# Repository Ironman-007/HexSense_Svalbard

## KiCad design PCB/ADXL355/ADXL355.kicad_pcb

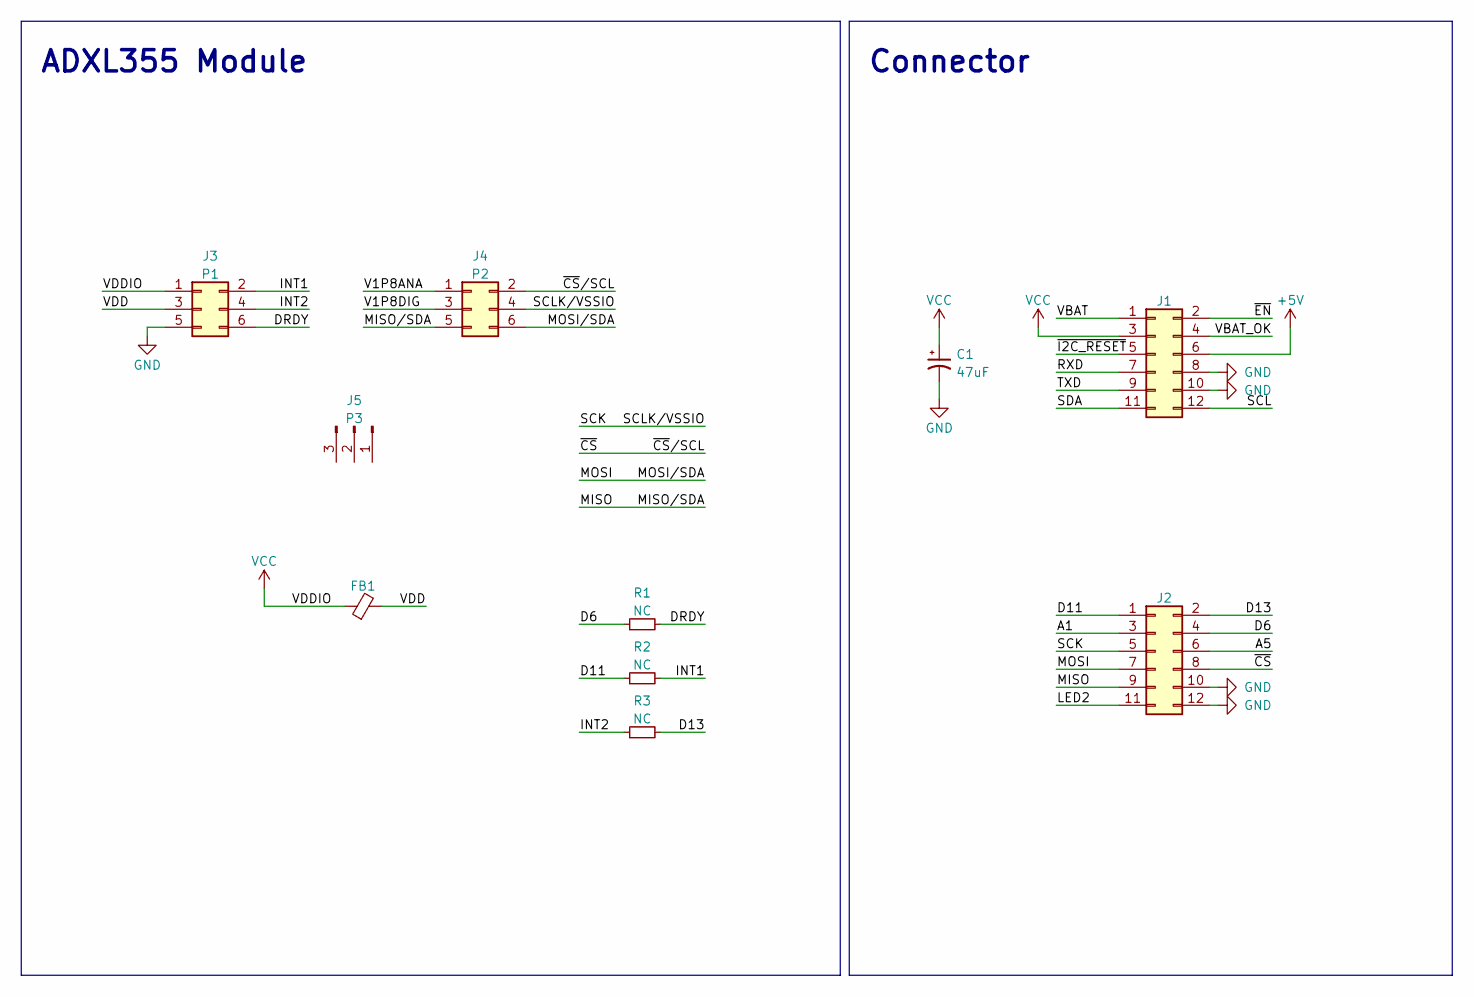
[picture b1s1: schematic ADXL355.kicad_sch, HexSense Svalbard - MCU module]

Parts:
C1: 47uF; LED_0805_2012Metric_Pad1.15x1.40mm_HandSolder
FB1: FerriteBead_Small; R_0603_1608Metric_Pad0.98x0.95mm_HandSolder
J1, J2: Conn_02x06_Odd_Even; PinHeader_2x06_P2.54mm_Vertical
J3: P1; PinHeader_2x03_P2.54mm_Vertical
J4: P2; PinHeader_2x03_P2.54mm_Vertical
J5: P3; PinHeader_1x03_P2.54mm_Vertical
R1, R2, R3: NC; R_0805_2012Metric

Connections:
+5V: J1.6
/A1: J2.3
/A5: J2.6
/D6: J2.4, R1.1
/D11: J2.1, R2.1
/D13: J2.2, R3.2
/DRDY: J3.6, R1.2
/INT1: J3.2, R2.2
/INT2: J3.4, R3.1
/LED2: J2.11
/MISO: J2.9, J4.5
/MOSI: J2.7, J4.6
/RXD: J1.7
/SCK: J2.5, J4.4
/SCL: J1.12
/SDA: J1.11
/TXD: J1.9
/V1P8ANA: J4.1
/V1P8DIG: J4.3
/VBAT: J1.1
/VBAT_OK: J1.4
/VDD: FB1.2, J3.3
/~CS: J2.8, J4.2
/~EN: J1.2
/~I2C_RESET: J1.5
GND: C1.2, J1.8, J1.10, J2.10, J2.12, J3.5
VCC: C1.1, FB1.1, J1.3, J3.1

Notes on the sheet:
ADXL355 Module
Connector

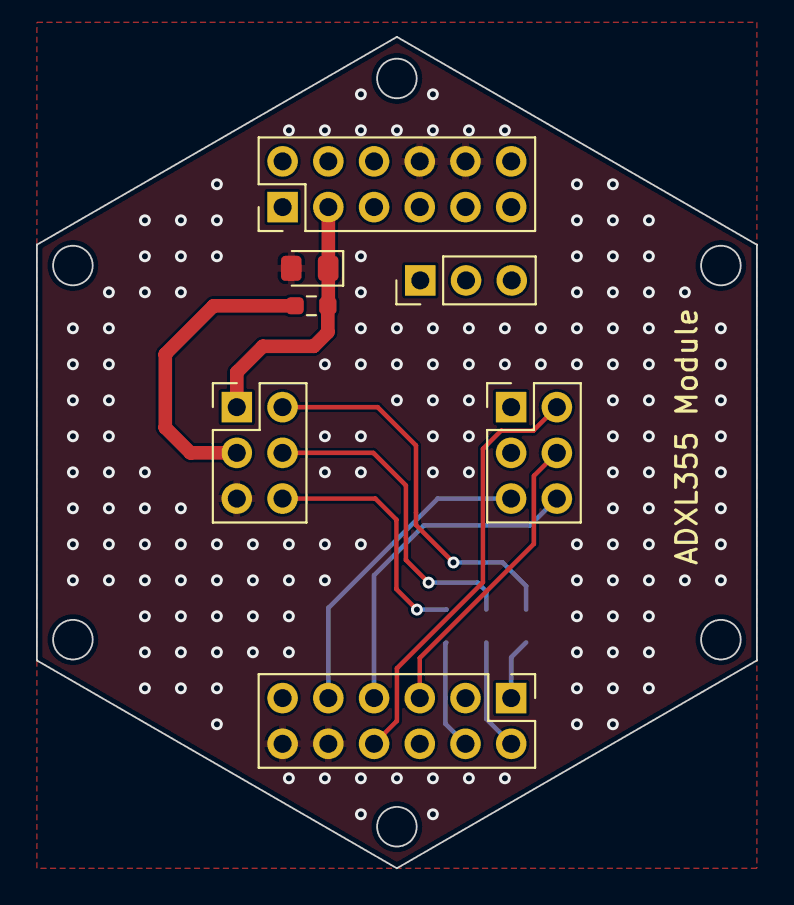
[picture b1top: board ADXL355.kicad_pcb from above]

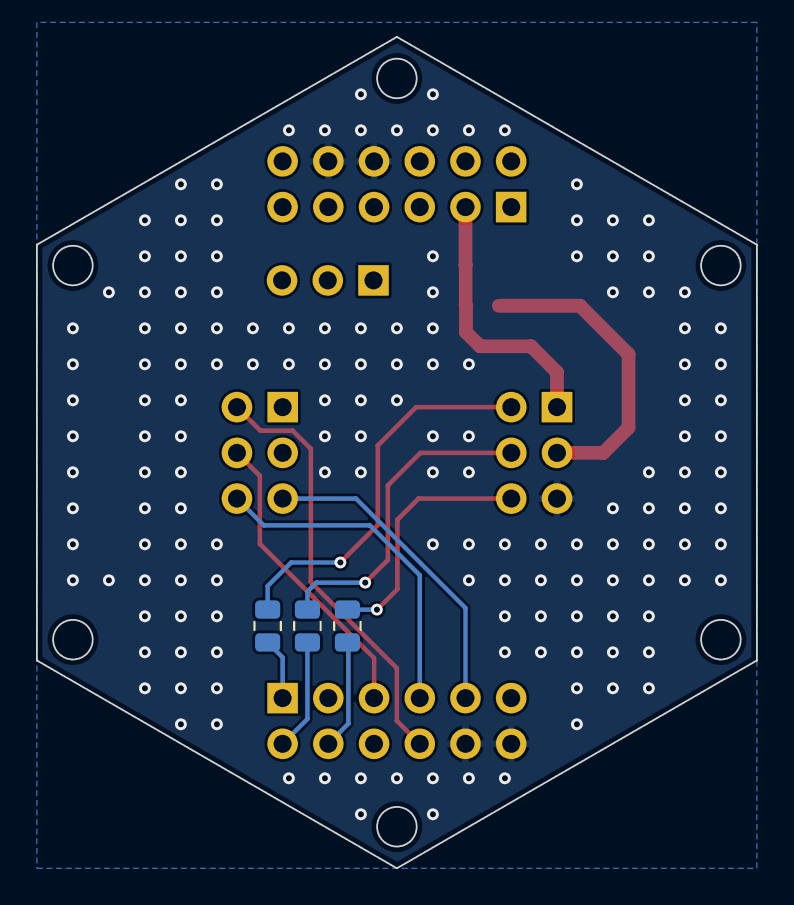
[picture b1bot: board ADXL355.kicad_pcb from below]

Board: 2 copper layers, 40.0 x 46.2 mm, 10 parts (3 on the bottom side), 13 nets.

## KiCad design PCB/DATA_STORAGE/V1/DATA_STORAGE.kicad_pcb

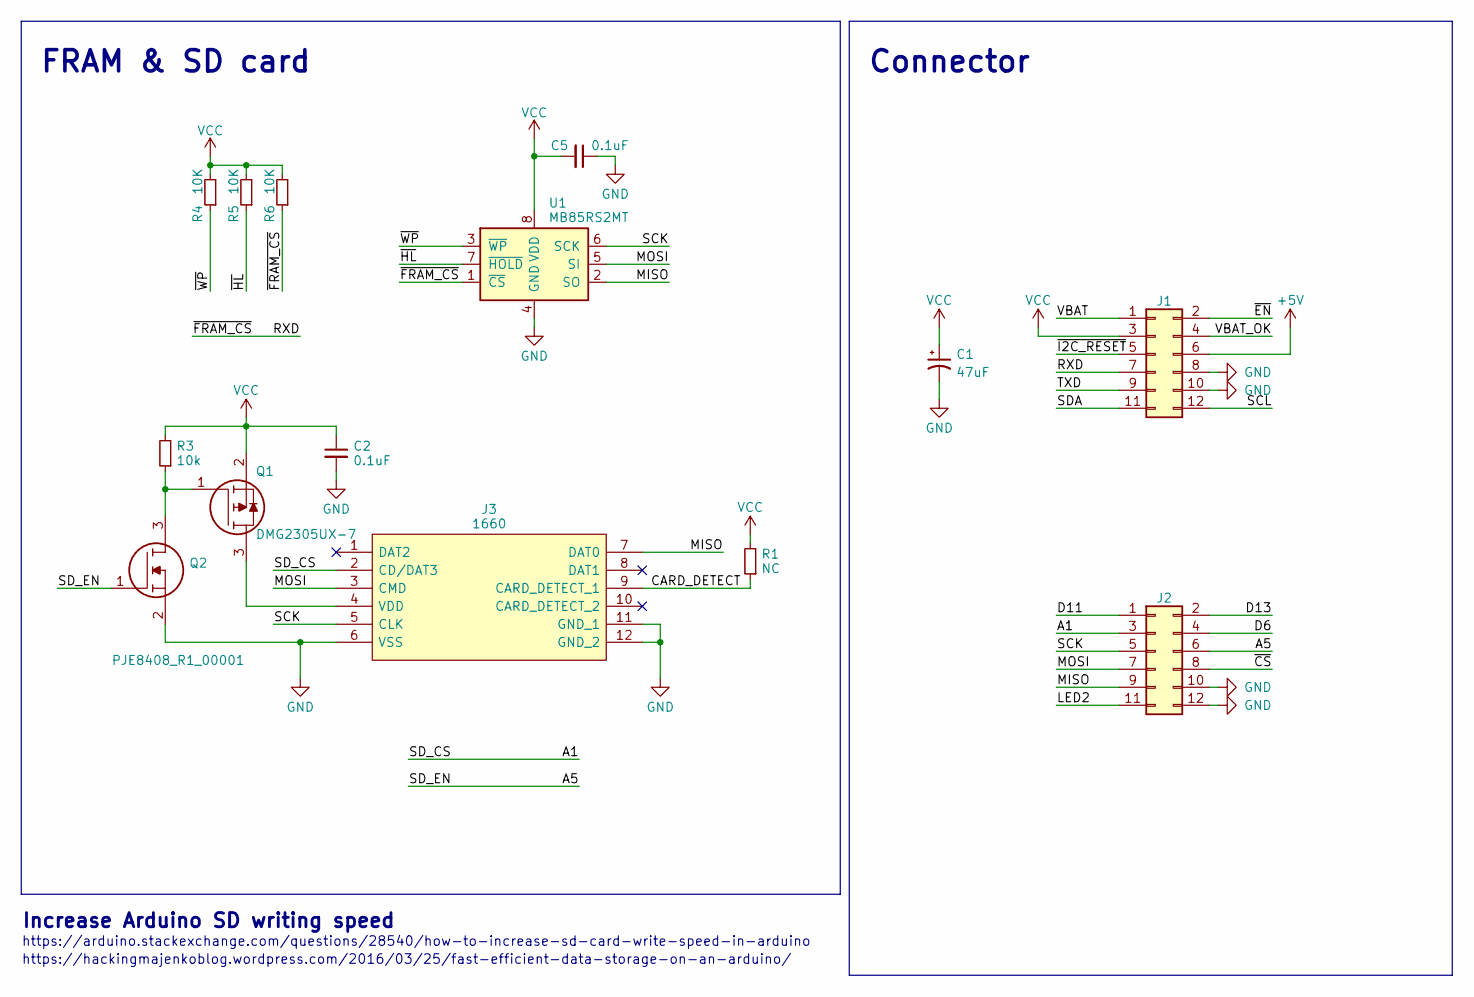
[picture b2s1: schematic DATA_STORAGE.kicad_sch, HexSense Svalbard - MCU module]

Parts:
C1: 47uF; LED_0805_2012Metric_Pad1.15x1.40mm_HandSolder
C2, C5: 0.1uF; C_0603_1608Metric_Pad1.08x0.95mm_HandSolder
J1, J2: Conn_02x06_Odd_Even; PinHeader_2x06_P2.54mm_Vertical
J3: 1660; Manufacturer_Part_Number 1660; Mouser Part Number 485-1660
Q1: DMG2305UX-7; SOT96P240X110-3N; Manufacturer_Part_Number DMG2305UX-7; Mouser Part Number 621-DMG2305UX-7
Q2: PJE8408_R1_00001; SOTFL50P160X60-3N; Manufacturer_Part_Number PJE8408_R1_00001; Mouser Part Number 241-PJE8408_R1_00001
R1: NC; R_0603_1608Metric_Pad0.98x0.95mm_HandSolder
R3: 10k; R_0603_1608Metric_Pad0.98x0.95mm_HandSolder
R4, R5, R6: 10K; R_0603_1608Metric_Pad0.98x0.95mm_HandSolder
U1: MB85RS2MT; SSOP-8_3.9x5.05mm_P1.27mm

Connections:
+5V: J1.6
/A1: J2.3, J3.2 (CD/DAT3)
/A5: J2.6, Q2.1
/CARD_DETECT: J3.9 (CARD_DETECT_1), R1.1
/D6: J2.4
/D11: J2.1
/D13: J2.2
/LED2: J2.11
/MISO: J2.9, J3.7 (DAT0), U1.2 (SO)
/MOSI: J2.7, J3.3 (CMD), U1.5 (SI)
/RXD: J1.7, R6.1, U1.1 (~CS)
/SCK: J2.5, J3.5 (CLK), U1.6 (SCK)
/SCL: J1.12
/SDA: J1.11
/TXD: J1.9
/VBAT: J1.1
/VBAT_OK: J1.4
/~CS: J2.8
/~EN: J1.2
/~HL: R5.1, U1.7 (~HOLD)
/~I2C_RESET: J1.5
/~WP: R4.1, U1.3 (~WP)
GND: C1.2, C2.2, C5.1, J1.8, J1.10, J2.10, J2.12, J3.6 (VSS), J3.11 (GND_1), J3.12 (GND_2), Q2.2, U1.4 (GND)
unnamed: J3.4 (VDD), Q1.3
unnamed: Q1.1, Q2.3, R3.1
VCC: C1.1, C2.1, C5.2, J1.3, Q1.2, R1.2, R3.2, R4.2, R5.2, R6.2, U1.8 (VDD)

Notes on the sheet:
https://arduino.stackexchange.com/questions/28540/how-to-increase-sd-card-write-speed-in-arduino
FRAM & SD card
Increase Arduino SD writing speed
https://hackingmajenkoblog.wordpress.com/2016/03/25/fast-efficient-data-storage-on-an-arduino/
Connector

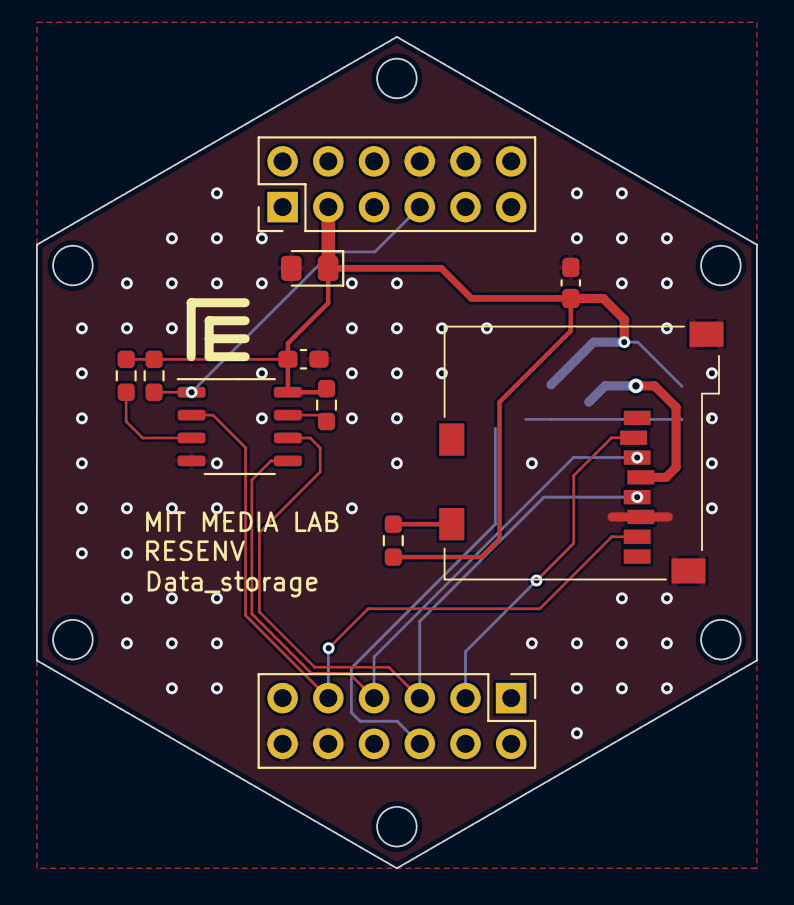
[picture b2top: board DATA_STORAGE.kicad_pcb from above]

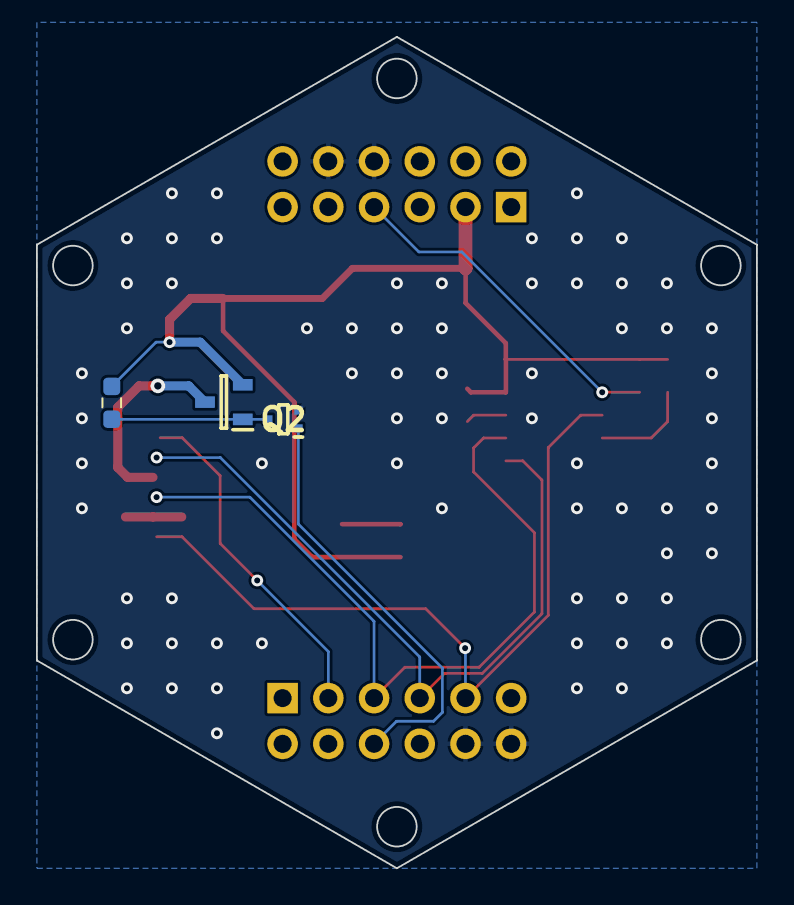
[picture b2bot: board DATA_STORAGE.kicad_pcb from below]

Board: 2 copper layers, 40.0 x 46.2 mm, 14 parts (3 on the bottom side), 13 nets.

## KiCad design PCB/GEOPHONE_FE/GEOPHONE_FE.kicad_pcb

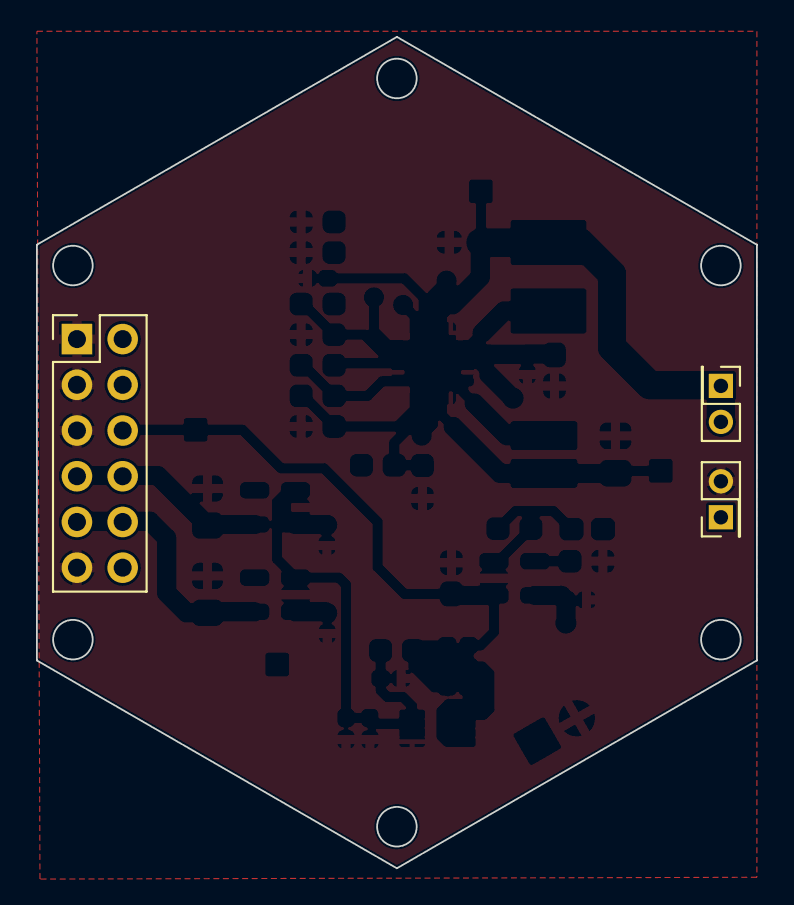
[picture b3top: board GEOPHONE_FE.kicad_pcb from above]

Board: 2 copper layers, 40.0 x 46.2 mm, 3 parts (0 on the bottom side), 5 nets, no tracks yet.

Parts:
J2: Conn_02x06_Odd_Even; PinHeader_2x06_P2.54mm_Vertical
J3: Battery; PinHeader_2x01_P2.00mm_Vertical
J4: Solar cell; PinHeader_2x01_P2.00mm_Vertical

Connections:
+1V8: J2.9, J2.10
+3V3: J2.7, J2.8
/SC: J4.1, J4.2
/VBAT: J2.6, J3.1
GND: J2.1, J2.3, J2.5, J2.11, J3.2

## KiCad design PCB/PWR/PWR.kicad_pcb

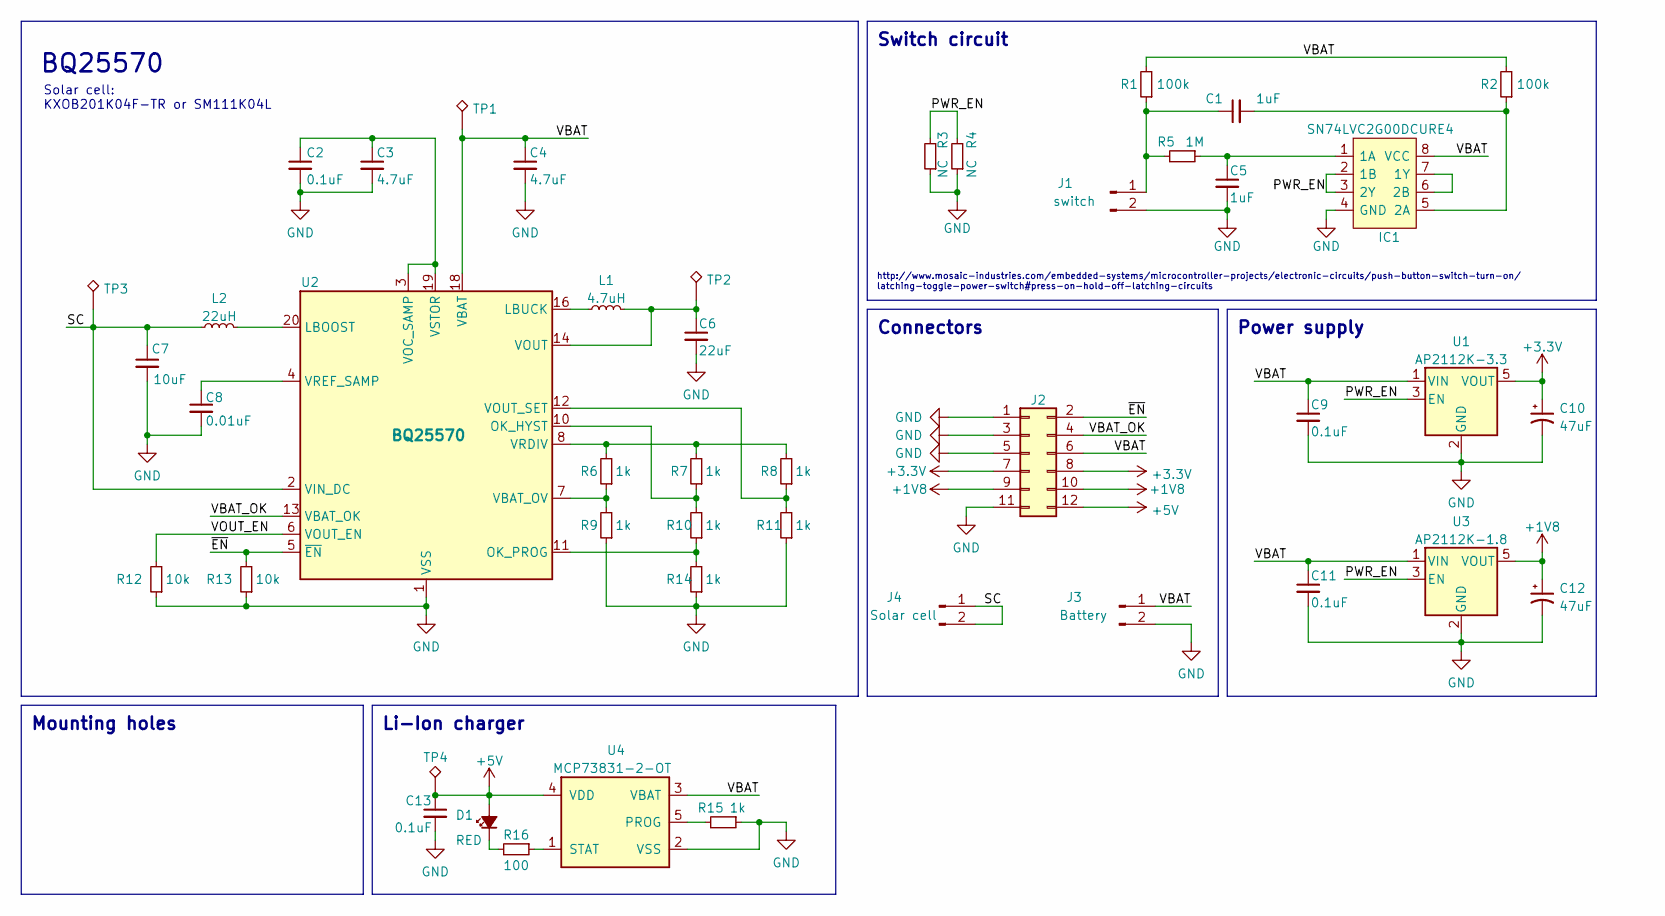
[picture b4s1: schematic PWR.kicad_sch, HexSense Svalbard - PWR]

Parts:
C1, C5: 1uF; C_0402_1005Metric_Pad0.74x0.62mm_HandSolder
C2, C9, C11, C13: 0.1uF; C_0402_1005Metric_Pad0.74x0.62mm_HandSolder
C3, C4: 4.7uF; C_0603_1608Metric_Pad1.08x0.95mm_HandSolder
C6: 22uF; C_0805_2012Metric_Pad1.18x1.45mm_HandSolder
C7: 10uF; C_0603_1608Metric_Pad1.08x0.95mm_HandSolder
C8: 0.01uF; C_0402_1005Metric_Pad0.74x0.62mm_HandSolder
C10, C12: 47uF; LED_0805_2012Metric_Pad1.15x1.40mm_HandSolder
D1: RED; LED_0603_1608Metric_Pad1.05x0.95mm_HandSolder
IC1: SN74LVC2G00DCURE4; SOP50P310X90-8N; Manufacturer_Part_Number SN74LVC2G00DCURE4
J1: switch; PinHeader_1x02_P2.54mm_Vertical
J2: Conn_02x06_Odd_Even; PinHeader_2x06_P2.54mm_Vertical
J3: Battery; PinHeader_2x01_P2.00mm_Vertical
J4: Solar cell; PinHeader_2x01_P2.00mm_Vertical
L1: 4.7uH; L_Wuerth_MAPI-3015
L2: 22uH; L_Taiyo-Yuden_NR-40xx_HandSoldering
R1, R2: 100k; R_0402_1005Metric_Pad0.72x0.64mm_HandSolder
R3, R4: NC; R_0402_1005Metric_Pad0.72x0.64mm_HandSolder
R5: 1M; R_0603_1608Metric_Pad0.98x0.95mm_HandSolder
R6, R7, R8, R9, R10, R11, R14, R15: 1k; R_0603_1608Metric_Pad0.98x0.95mm_HandSolder
R12, R13: 10k; R_0603_1608Metric_Pad0.98x0.95mm_HandSolder
R16: 100; R_0603_1608Metric_Pad0.98x0.95mm_HandSolder
TP1, TP2, TP3, TP4: TestPoint_Alt; TestPoint_Pad_1.0x1.0mm
U1: AP2112K-3.3; SOT-23-5
U2: BQ25570; QFN-20-1EP_3.5x3.5mm_P0.5mm_EP2x2mm
U3: AP2112K-1.8; SOT-23-5
U4: MCP73831-2-OT; SOT-23-5

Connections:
+1V8: C12.1, J2.9, J2.10, U3.5 (VOUT)
+3V3: C10.1, J2.7, J2.8, U1.5 (VOUT)
+5V: C13.1, D1.2 (A), J2.12, TP4.1, U4.4 (VDD)
/PWR_EN: IC1.2 (1B), IC1.3 (2Y), R3.2, R4.2, U1.3 (EN), U3.3 (EN)
/SC: C7.1, J4.1, J4.2, L2.1, TP3.1, U2.2 (VIN_DC)
/VBAT: C4.1, C9.1, C11.1, IC1.8 (VCC), J2.6, J3.1, R1.2, R2.2, TP1.1, U1.1 (VIN), U2.18 (VBAT), U3.1 (VIN), U4.3 (VBAT)
/VBAT_OK: J2.4, U2.13 (VBAT_OK)
/VOUT_EN: R12.2, U2.6 (VOUT_EN)
/~EN: J2.2, R13.2, U2.5 (~EN)
GND: C2.2, C3.2, C4.2, C5.2, C6.2, C7.2, C8.2, C9.2, C10.2, C11.2, C12.2, C13.2, IC1.4 (GND), J1.2, J2.1, J2.3, J2.5, J2.11, J3.2, R3.1, R4.1, R9.1, R11.1, R12.1, R13.1, R14.1, R15.1, U1.2 (GND), U2.1 (VSS), U2.9 (VSS), U2.15 (VSS), U2.17 (VSS), U2.21 (VSS), U3.2 (GND), U4.2 (VSS)
unnamed: C1.1, J1.1, R1.1, R5.2
unnamed: C1.2, IC1.5 (2A), R2.1
unnamed: C2.1, C3.1, U2.3 (VOC_SAMP), U2.19 (VSTOR)
unnamed: C5.1, IC1.1 (1A), R5.1
unnamed: C6.1, L1.2, TP2.1, U2.14 (VOUT)
unnamed: C8.1, U2.4 (VREF_SAMP)
unnamed: D1.1 (K), R16.2
unnamed: IC1.6 (2B), IC1.7 (1Y)
unnamed: L1.1, U2.16 (LBUCK)
unnamed: L2.2, U2.20 (LBOOST)
unnamed: R6.1, R9.2, U2.7 (VBAT_OV)
unnamed: R6.2, R7.2, R8.2, U2.8 (VRDIV)
unnamed: R10.1, R14.2, U2.11 (OK_PROG)
unnamed: R7.1, R10.2, U2.10 (OK_HYST)
unnamed: R8.1, R11.2, U2.12 (VOUT_SET)
unnamed: R15.2, U4.5 (PROG)
unnamed: R16.1, U4.1 (STAT)

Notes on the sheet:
Li-Ion charger
BQ25570
Switch circuit
Mounting holes
Solar cell: KXOB201K04F-TR or SM111K04L
Power supply
http://www.mosaic-industries.com/embedded-systems/microcontroller-projects/electronic-circuits/push-button-switch-turn-on/ latching-toggle-power-switch#press-on-hold-off-latching-circuits
Connectors

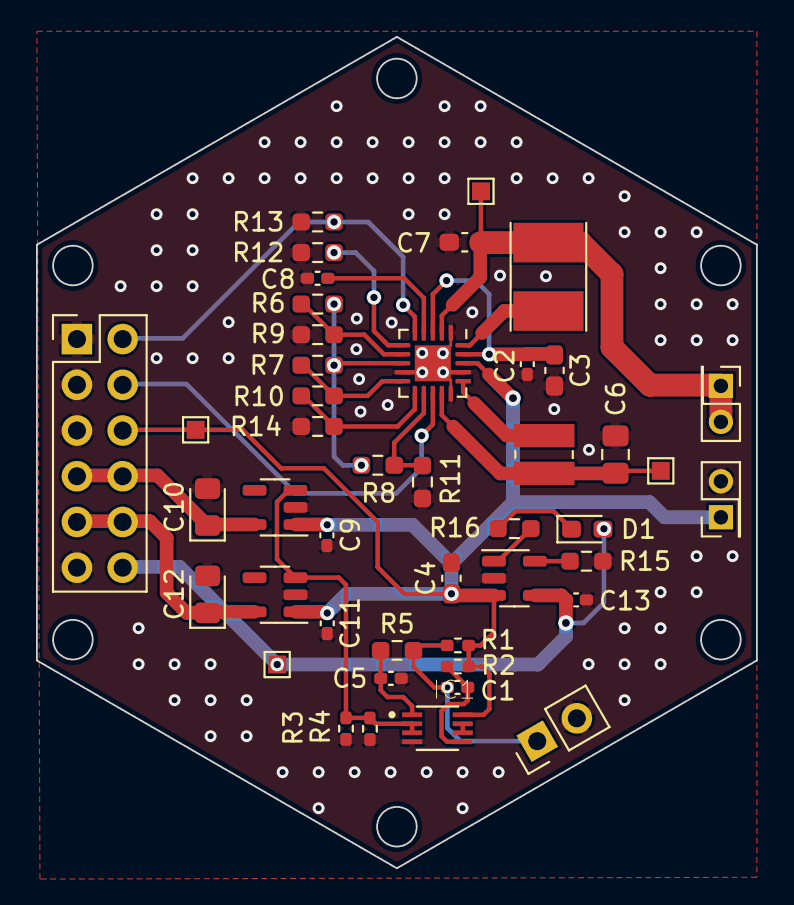
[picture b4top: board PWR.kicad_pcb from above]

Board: 2 copper layers, 40.0 x 46.2 mm, 45 parts (0 on the bottom side), 27 nets.

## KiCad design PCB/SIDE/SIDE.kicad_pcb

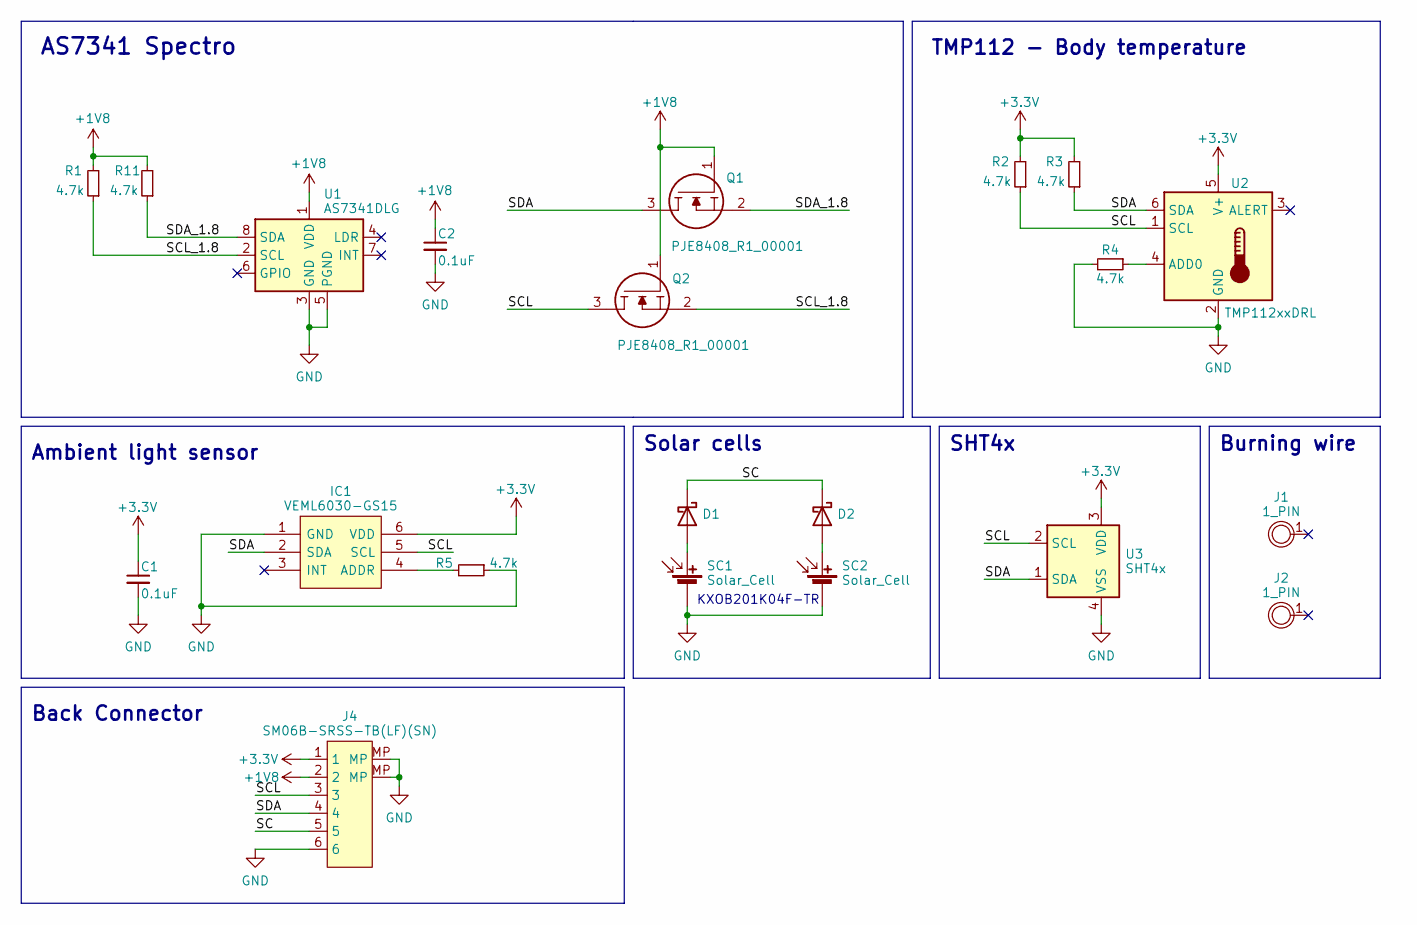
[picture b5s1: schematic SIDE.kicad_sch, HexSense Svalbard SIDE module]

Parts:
C1, C2: 0.1uF; C_0603_1608Metric_Pad1.08x0.95mm_HandSolder
D1, D2: D_Schottky; D_0805_2012Metric_Pad1.15x1.40mm_HandSolder
IC1: VEML6030-GS15; VEML6030GS15; Manufacturer_Part_Number VEML6030-GS15; Mouser Part Number 78-VEML6030-GS15
J1, J2: 1_PIN; 1_pin_SMD_1.5mmx1.0mm
J4: SM06B-SRSS-TB(LF)(SN); JST_SH_SM06B-SRSS-TB_1x06-1MP_P1.00mm_Horizontal
Q1, Q2: PJE8408_R1_00001; SOTFL50P160X60-3N; Manufacturer_Part_Number PJE8408_R1_00001; Mouser Part Number 241-PJE8408_R1_00001
R1, R2, R3, R4, R5, R11: 4.7k; R_0603_1608Metric_Pad0.98x0.95mm_HandSolder
SC1, SC2: Solar_Cell; KXOB201K04F-TR
U1: AS7341DLG; AMS_OLGA-8_2x3.1mm_P0.8mm
U2: TMP112xxDRL; SOT-563
U3: SHT4x; Sensirion_DFN-4_1.5x1.5mm_P0.8mm_SHT4x_NoCentralPad

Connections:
+1V8: C2.1, J4.2, Q1.1, Q2.1, R1.2, R11.2, U1.1 (VDD)
+3V3: C1.1, IC1.6 (VDD), J4.1, R2.2, R3.2, U2.5 (V+), U3.3 (VDD)
/SC: D1.1 (K), D2.1 (K), J4.5
/SCL: IC1.5 (SCL), J4.3, Q2.3, R2.1, U2.1 (SCL), U3.2 (SCL)
/SCL_1.8: Q2.2, R1.1, U1.2 (SCL)
/SDA: IC1.2 (SDA), J4.4, Q1.3, R3.1, U2.6 (SDA), U3.1 (SDA)
/SDA_1.8: Q1.2, R11.1, U1.8 (SDA)
GND: C1.2, C2.2, IC1.1 (GND), J4.6, J4.MP, R4.2, R5.1, SC1.2 (-), SC2.2 (-), U1.3 (GND), U1.5 (PGND), U2.2 (GND), U3.4 (VSS)
unnamed: D1.2 (A), SC1.1 (+)
unnamed: D2.2 (A), SC2.1 (+)
unnamed: IC1.4 (ADDR), R5.2
unnamed: R4.1, U2.4 (ADD0)

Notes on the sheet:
Burning wire
Back Connector
TMP112 - Body temperature
KXOB201K04F-TR
Solar cells
SHT4x
AS7341 Spectro
Ambient light sensor

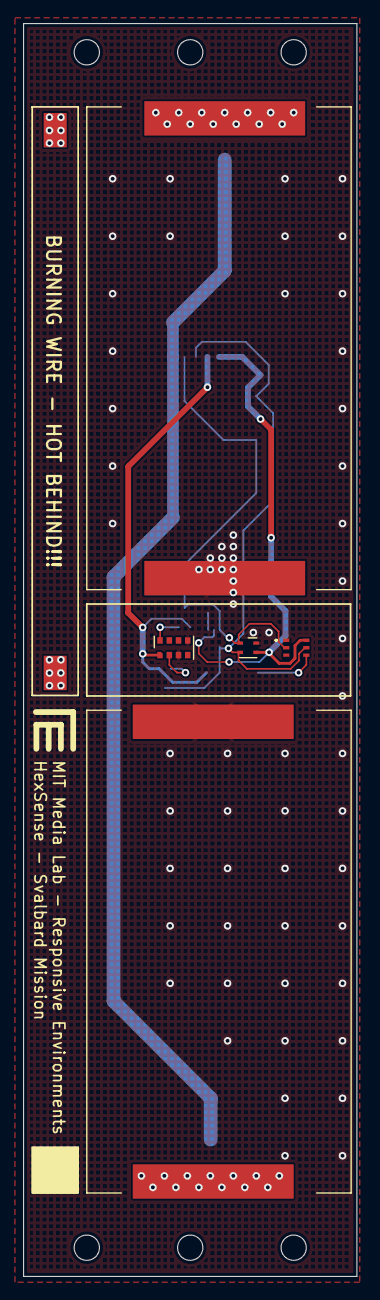
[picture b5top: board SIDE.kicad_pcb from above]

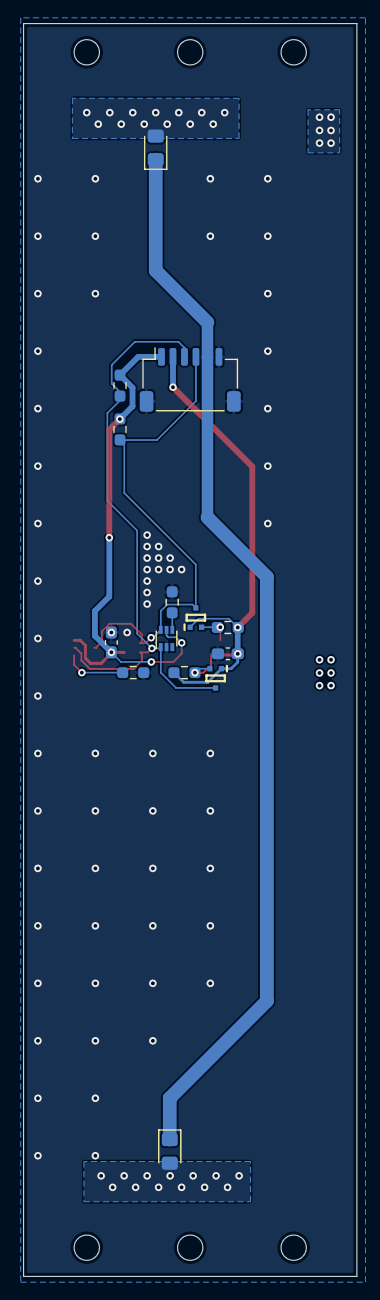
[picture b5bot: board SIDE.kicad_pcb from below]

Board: 2 copper layers, 29.0 x 109.0 mm, 21 parts (14 on the bottom side), 12 nets.
